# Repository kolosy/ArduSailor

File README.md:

ArduSailor
==========
ArduSailor is an autonomous sail boat project based on the Arduino platform. Using a modified Arduino Mega board (schematics under `layout`), ArduSailor can be programmed with a set of GPS waypoints that it can then sail to.

The platform is built around a simple, two-servo sail boat design, with a winch servo for sail plan control and a rudder servo for steering. The circuit layout included is for a modified Arduino Mega 2560, which includes:

* A 9DOF IMU (an Invensense MPU9250)
* A break-out for a weather vane (this circuit is also included)
* A microSD card
* Two servo breakouts
* Three power regulators (one to provide 6V for the servos, one to provide 3.3V for the rest and one MPPT solar charger for the LiPo)
* A GPS chip (Venus 638FPLx)
* A breakout for a UART-based camera module (currently unused)
* A battery input (currently running from a 3S LiPo battery pack)
* A breakout for the main UART port for logging (on my build I have this routed to a 433MHz radio module)
* ICSP header for programming

The included firmware operates off of a list of GPS waypoints. The pilot steers straight for the next waypoint when it can. When the waypoint is upwind (within `IRONS` of the wind), it beats: close-hauled, zigzagging up a corridor `CORRIDOR` metres either side of the line from where the leg started to the waypoint, tacking at the corridor's edges, until it can lay the waypoint on one tack. To tack, it comes up to just outside the no-go zone (`TACK_MARGIN`) and goes through the wind from there, with way on (`MIN_TACK_SPEED`). If it can't get up to speed there, or its last two tacks ended in irons (`MAX_TACK_TRIES`), it goes round by gybing instead. Whenever the waypoint can be reached on the tack it's on, it steers straight for it. If the boat stops (in irons, or drifting backwards), it lets the sheet out and falls off (`RECOVER_ANGLE`) on whichever tack it's on, steering the other way while it's going backwards. It then stays on that tack, sailing a little free until it's back up to speed, rather than tacking straight back into irons. Outside a beat there is no cross-track correction.

Simulator
=========
`sim/` builds the firmware for your computer and sails it around a simulated course, with the boat, wind, waves and sensors shown in a browser. You can change the conditions, the PID gains and the firmware's settings while it runs. On a Mac (after `xcode-select --install`):

    python3 sim/run.py

See [sim/README.md](sim/README.md).

Status
======
I've built several iterations of the circuit board, and it works reliably. When at speed, the navigation works .. somewhat. My current testing is in a sub-optimal body of water (a long, narrow channel), making certain tests difficult.

Here's what I need to tackle

Short-term
----------
* Finish debugging basic piloting and navigation.
* Add cross-track correction
* Add heel compensation
* Add camera module support

Longer-term
-----------
* Improve the navigation algorithm to include no-go zones
* Add wind speed sensor (hw)

Pie-in-the-sky
--------
I'd like to replace the pilot code entirely with AI. This should be reduce-able to an optimization problem... but that's a bit beyond me right now.

Enjoy!

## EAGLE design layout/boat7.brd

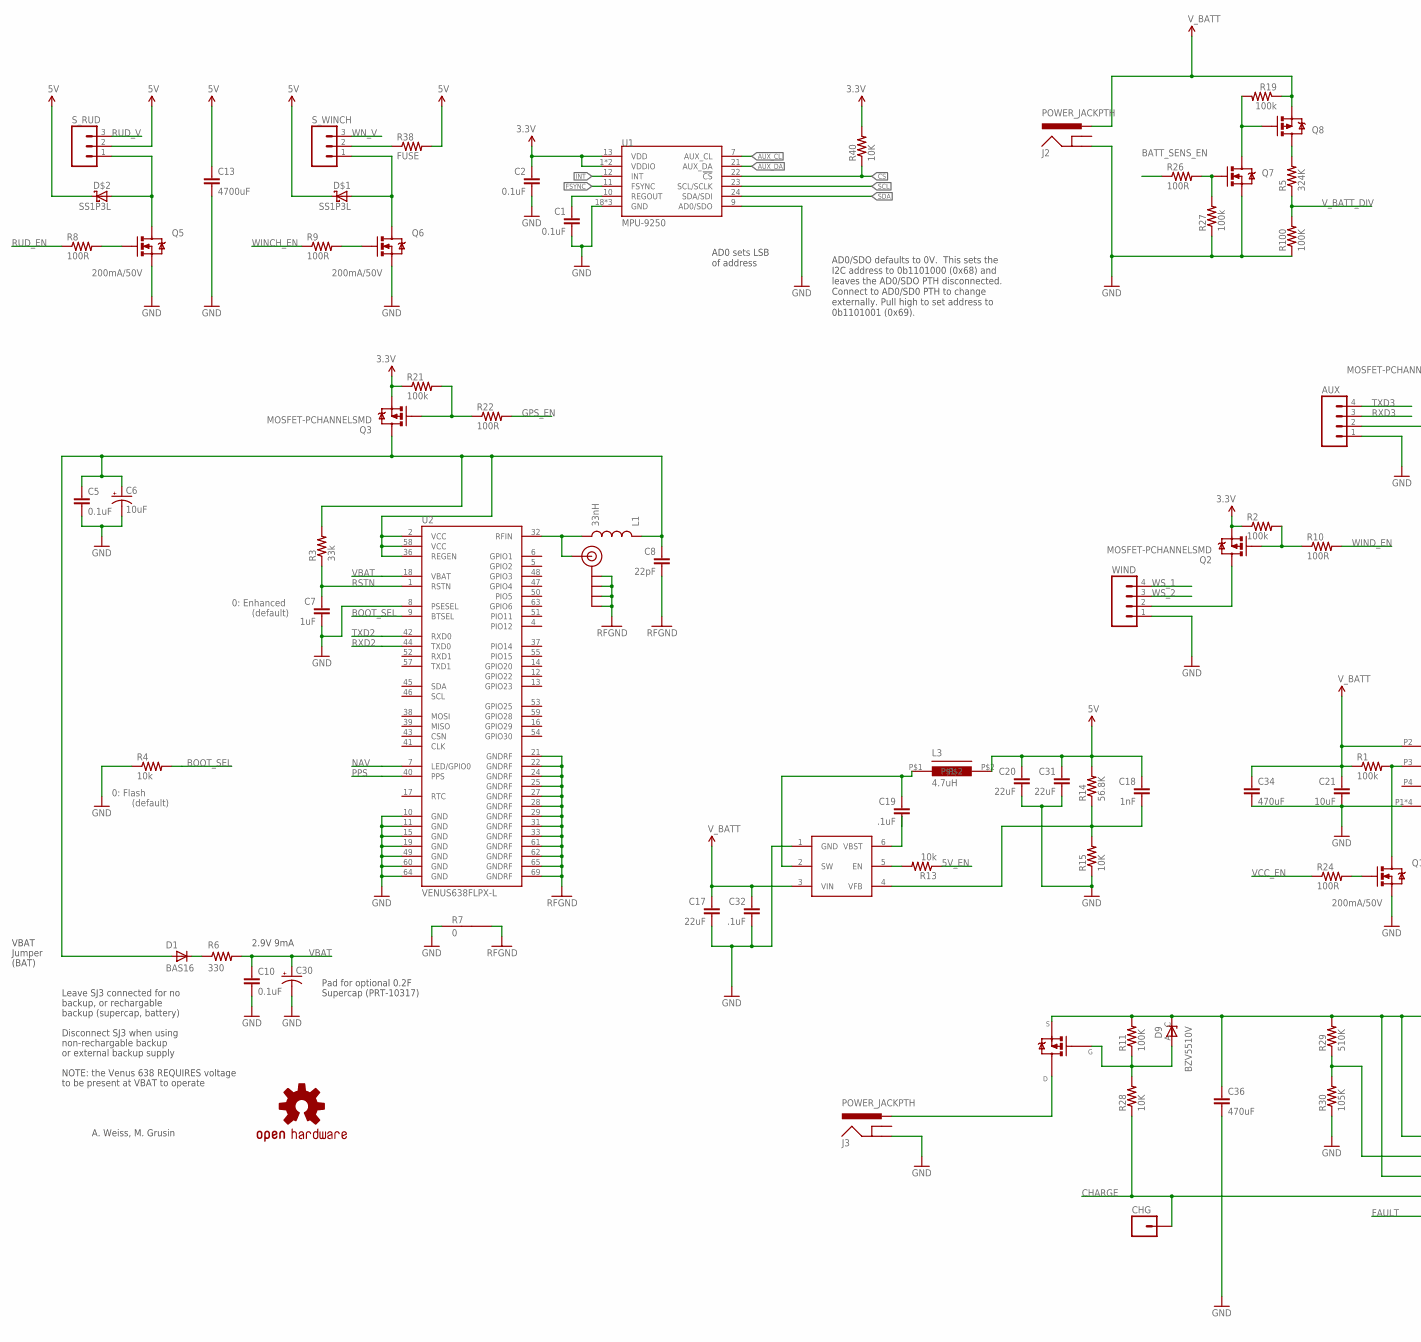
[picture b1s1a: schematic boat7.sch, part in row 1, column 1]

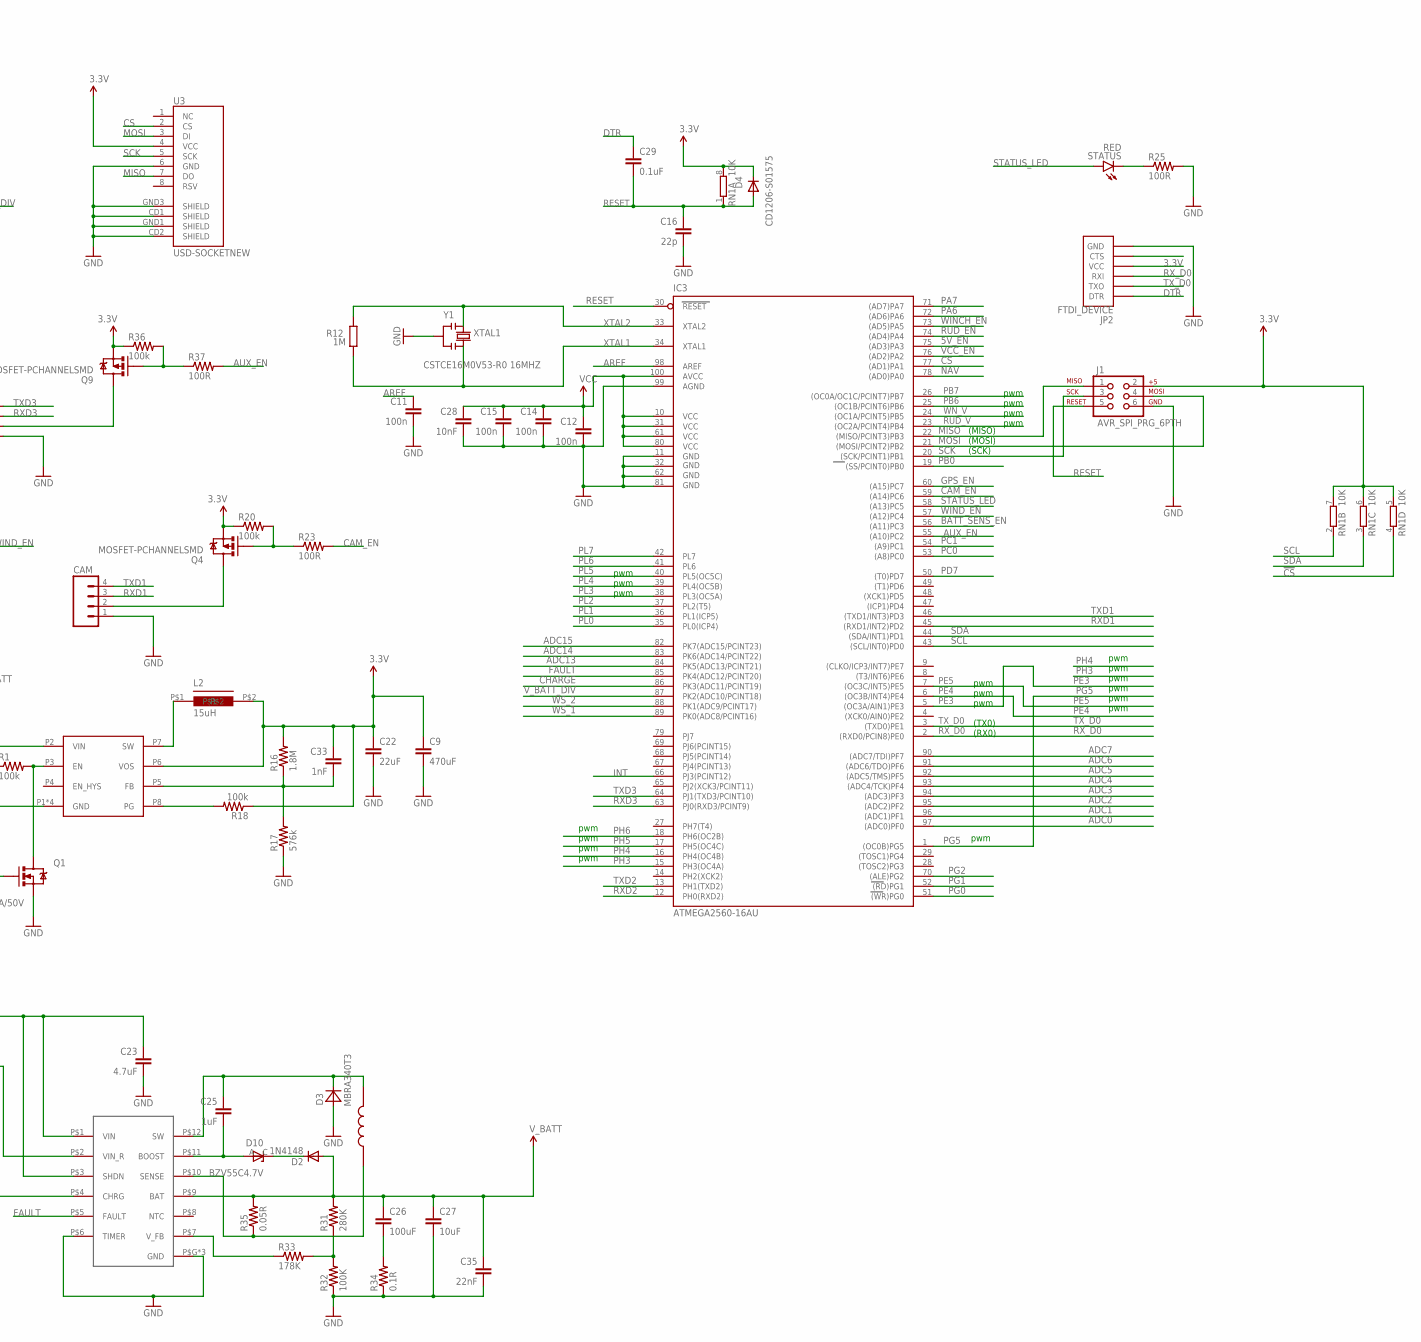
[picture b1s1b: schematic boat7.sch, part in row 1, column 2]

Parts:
AUX: M04PTH; 1X04
C1, C2, C5, C10, C29: 0.1uF; 0603-CAP
C6: 10uF; EIA3216
C7: 1uF; 0603-CAP
C8: 22pF; 0603-CAP
C9, C34, C36: 470uF; CAP-PTH-5MM
C11, C12, C14, C15: 100n; C0603-ROUND
C13: 4700uF; CAP-PTH-5MM
C16: 22p; C0603-ROUND
C17, C20, C31: 22uF; 1206
C18: 1nF; 0805
C19, C32: .1uF; 0805
C21: 10uF; 0805
C22: 22uF; 0805
C23: 4.7uF; 1206
C25: 1uF; 0805
C26: 100uF; 1210
C27: 10uF; 1210
C28: 10nF; 0603-CAP
C30: CAP_POL; DSK-621
C33: 1nF; 0402-CAP
C35: 22nF; 0805
CAM: M04PTH; 1X04
CHG: M01PTH; 1X01
D1: BAS16; SOD-323
D2: 1N4148; MINIMELF
D3: MBRA340T3; SMA
D4: CD1206-S01575; SOD323-R
D9: BZV5510V; MINIMELF
D10: BZV55C4.7V; MINIMELF
D$1, D$2: SS1P3L; MICROSMP
IC3: ATMEGA2560-16AU; TQFP100
J1: AVR_SPI_PRG_6PTH; 2X3
J2, J3: POWER_JACKPTH; POWER_JACK_PTH
JP2: FTDI_DEVICE; FTDI_DEVICE_SIDE
JP5: SMA_EDGE; SMA-EDGE
L1: 33nH; 0603
L2: 15uH; VLCF4020
L3: 4.7uH; SLF7055
Q1, Q5, Q6, Q7: 200mA/50V; SOT23-3
Q2, Q3, Q4, Q8, Q9: MOSFET-PCHANNELSMD; SOT23-3
R1, R2, R18, R19, R20, R21, R27, R36: 100k; 0603-RES
R3: 33k; 0603-RES
R4, R13: 10k; 0603-RES
R5: 324K; 0603-RES
R6: 330; 0603-RES
R7: 0; GND-JUMP
R8, R9, R10, R22, R23, R24, R25, R26, R37: 100R; 0603-RES
R11, R32, R100: 100K; 0603-RES
R12: 1M; R0603-ROUND
R14: 56.8K; 0603-RES
R15, R28, R40: 10K; 0603-RES
R16: 1.8M; 0603-RES
R17: 576k; 0603-RES
R29: 510K; 0603-RES
R30: 105K; 0603-RES
R31: 280K; 0603-RES
R33: 178K; 0603-RES
R34: 0.1R; 1206
R35: 0.05R; 1206
R38: FUSE; AXIAL-0.1
RN1: 10K; CAT16
STATUS: RED; LED-0603
S_RUD: M03PTH; 1X03
S_WINCH: M03PTH; 1X03
U1: MPU-9250; QFN24_PAD
U2: VENUS638FLPX-L; VENUS638FLPX
U3: USD-SOCKETNEW; MICRO-SD-SOCKET-PP
U$1: TPS62125; S-PWSON-N8
U$2: TPS56X200; SOT23-6
U$4: OSHW-LOGOS; OSHW-LOGO-S
U$5: LT365212; 12-LEAD-MSOP-EXPOSED
U$7: B82464G4
U$15: SI4401DDY; SOIC-8
WIND: M04PTH; 1X04
Y1: CSTCE16M0V53-R0 16MHZ; RESONATOR

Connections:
3.3V: C2.1, C9.1, C12.1, C14.1, C15.1, C22.1, C28.1, C33.1, D4.C, IC3.10 (VCC), IC3.31 (VCC1), IC3.61 (VCC2), IC3.80 (VCC3), IC3.100 (AVCC), J1.2, JP2.P$4 (VCC), L2.P$2, Q2.2 (S), Q3.2 (S), Q4.2 (S), Q9.2 (S), R2.1, R16.2, R18.1, R20.1, R21.1, R36.1, R40.2, RN1.5 (2), RN1.6 (2), RN1.7 (2), RN1.8 (2), U1.1 (VDDIO), U1.8 (VDDIO), U1.13 (VDD), U3.4 (VCC), U$1.P6 (VOS)
5V: C13.1, C18.1, C20.1, C31.1, D$1.C, D$2.C, L3.P$2, R14.2, R38.P$2 (2), S_RUD.2
5V_EN: IC3.75 ((AD3)PA3), R13.1
!CS: R40.1, RN1.4 (1), U1.22 (!CS)
ADC0: IC3.97 ((ADC0)PF0)
ADC1: IC3.96 ((ADC1)PF1)
ADC2: IC3.95 ((ADC2)PF2)
ADC3: IC3.94 ((ADC3)PF3)
ADC4: IC3.93 ((ADC4/TCK)PF4)
ADC5: IC3.92 ((ADC5/TMS)PF5)
ADC6: IC3.91 ((ADC6/TDO)PF6)
ADC7: IC3.90 ((ADC7/TDI)PF7)
ADC13: IC3.84 (PK5(ADC13/PCINT21))
ADC14: IC3.83 (PK6(ADC14/PCINT22))
ADC15: IC3.82 (PK7(ADC15/PCINT23))
ANT: JP5.SIG (SIGNAL), L1.2, U2.32 (RFIN)
AREF: C11.1, IC3.98 (AREF)
AUX_CL: U1.7 (AUX_CL)
AUX_DA: U1.21 (AUX_DA)
AUX_EN: IC3.55 ((A10)PC2), R37.2
BAT: C17.1, C21.1, C26.1, C27.1, C32.1, C34.1, C35.1, D2.A, J2.PWR, Q8.2 (S), R1.1, R19.1, R31.2, R35.2, U$1.P2 (VIN), U$2.3 (VIN), U$5.P$9 (BAT)
BATT_SENS_EN: IC3.56 ((A11)PC3), R26.1
BOOST: C25.2, D10.A, U$5.P$11 (BOOST)
BOOT_SEL: R4.2, U2.9 (BTSEL)
CAM_EN: IC3.59 ((A14)PC6), R23.2
CHARGE: CHG.1, IC3.86 (PK3(ADC11/PCINT19)), R28.1, U$5.P$4 (CHRG)
CS: IC3.77 ((AD1)PA1), U3.2 (CS)
DTR: C29.1, JP2.P$1 (DTR)
FAULT: IC3.85 (PK4(ADC12/PCINT20)), U$5.P$5 (FAULT)
FSYNC: U1.11 (FSYNC)
GND: AUX.1, C1.2, C2.2, C5.2, C6.C (-), C7.2, C9.2, C10.2, C11.2, C12.2, C13.2, C14.2, C15.2, C16.2, C17.2, C20.2, C21.2, C22.2, C23.2, C27.2, C28.2, C30.GND (-), C31.2, C32.2, C34.2, C35.2, C36.2, CAM.1, D3.A, IC3.11 (GND), IC3.32 (GND1), IC3.62 (GND2), IC3.81 (GND3), IC3.99 (AGND), J1.6, J2.GND, J3.GND, JP2.P$6 (GND), Q1.2 (S), Q5.2 (S), Q6.2 (S), Q7.2 (S), R4.1, R7.1, R15.1, R17.1, R25.2, R27.1, R30.1, R32.1, R34.1, R100.1, U1.9 (AD0/SDO), U1.18 (GND), U1.20 (GND), U1.CENTER (GND), U2.8 (PSESEL), U2.10 (GND), U2.11 (GND), U2.15 (GND), U2.19 (GND), U2.49 (GND), U2.60 (GND), U2.64 (GND), U3.6 (GND), U3.CD1 (SHIELD), U3.CD2 (SHIELD), U3.GND1 (SHIELD), U3.GND3 (SHIELD), U$1.P1 (GND), U$1.P_THERM (GND), U$1.P_THERM_VIA (GND), U$1.P_THERM_VIA1 (GND), U$2.1 (GND), U$5.P$6 (TIMER), U$5.P$G (GND), U$5.P$G1 (GND), U$5.P$G2 (GND), WIND.1, Y1.2
GPS_EN: IC3.60 ((A15)PC7), R22.2
GPS_PWR: C5.1, C6.A (+), C8.1, D1.2 (A), L1.1, Q3.3 (D), R3.2, U2.2 (VCC), U2.36 (REGEN), U2.58 (VCC)
INT: IC3.66 (PJ3(PCINT12)), U1.12 (INT)
MISO: IC3.22 ((MISO/PCINT3)PB3), J1.1, U3.7 (DO)
MOSI: IC3.21 ((MOSI/PCINT2)PB2), J1.4, U3.3 (DI)
unnamed: R38.P$1 (1), S_WINCH.2
unnamed: AUX.2, Q9.3 (D)
unnamed: C23.1, C36.1, D9.C (K), R11.2, R29.2, U$5.P$1 (VIN), U$5.P$3 (SHDN), U$15.1 (S), U$15.2 (S), U$15.3 (S)
unnamed: D1.1 (C), R6.1
unnamed: D9.A, R11.1, R28.2, U$15.4 (G)
unnamed: Q5.1 (G), R8.2
unnamed: D$1.A, Q6.3 (D), S_WINCH.1
unnamed: D$2.A, Q5.3 (D), S_RUD.1
unnamed: Q6.1 (G), R9.2
unnamed: C19.1, L3.P$1, U$2.2 (SW)
unnamed: Q9.1 (G), R36.2, R37.1
unnamed: R31.1, R32.2, R33.2
unnamed: L2.P$1, U$1.P7 (SW)
unnamed: R13.2, U$2.5 (EN)
unnamed: C33.2, R16.1, R17.2, U$1.P5 (FB)
unnamed: R18.2, U$1.P8 (PG)
unnamed: C18.2, R14.1, R15.2, U$2.4 (VFB)
unnamed: CAM.2, Q4.3 (D)
unnamed: Q4.1 (G), R20.2, R23.1
unnamed: Q3.1 (G), R21.2, R22.1
unnamed: Q1.3 (D), R1.2, U$1.P3 (EN)
unnamed: Q1.1 (G), R24.2
unnamed: Q2.3 (D), WIND.2
unnamed: R25.1, STATUS.C
unnamed: Q2.1 (G), R2.2, R10.1
unnamed: Q8.3 (D), R5.2
unnamed: Q7.3 (D), Q8.1 (G), R19.2
unnamed: Q7.1 (G), R26.2, R27.2
unnamed: C19.2, U$2.6 (VBST)
unnamed: C26.2, R34.2
unnamed: D2.C, D10.C (K)
NAV: IC3.78 ((AD0)PA0), U2.7 (LED/GPIO0)
PA6: IC3.72 ((AD6)PA6)
PA7: IC3.71 ((AD7)PA7)
PB0: IC3.19 ((SS/PCINT0)PB0)
PB6: IC3.25 ((OC1B/PCINT6)PB6)
PB7: IC3.26 ((OC0A/OC1C/PCINT7)PB7)
PC0: IC3.53 ((A8)PC0)
PC1: IC3.54 ((A9)PC1)
PD7: IC3.50 ((T0)PD7)
PE3: IC3.5 ((OC3A/AIN1)PE3)
PE4: IC3.6 ((OC3B/INT4)PE4)
PE5: IC3.7 ((OC3C/INT5)PE5)
PG0: IC3.51 ((WR)PG0)
PG1: IC3.52 ((RD)PG1)
PG2: IC3.70 ((ALE)PG2)
PG5: IC3.1 ((OC0B)PG5)
PH3: IC3.15 (PH3(OC4A))
PH4: IC3.16 (PH4(OC4B))
PH5: IC3.17 (PH5(OC4C))
PH6: IC3.18 (PH6(OC2B))
PL0: IC3.35 (PL0(ICP4))
PL1: IC3.36 (PL1(ICP5))
PL2: IC3.37 (PL2(T5))
PL3: IC3.38 (PL3(OC5A))
PL4: IC3.39 (PL4(OC5B))
PL5: IC3.40 (PL5(OC5C))
PL6: IC3.41 (PL6)
PL7: IC3.42 (PL7)
PPS: U2.40 (PPS)
REGOUT: C1.1, U1.10 (REGOUT)
RESET: C16.1, C29.2, D4.A, IC3.30 (RESET), J1.5, RN1.1
RFGND: C8.2, JP5.GND@0 (GND), JP5.GND@1 (GND), JP5.GND@2 (GND), JP5.GND@3 (GND), R7.2, U2.21 (GNDRF), U2.22 (GNDRF), U2.24 (GNDRF), U2.25 (GNDRF), U2.27 (GNDRF), U2.28 (GNDRF), U2.29 (GNDRF), U2.31 (GNDRF), U2.33 (GNDRF), U2.61 (GNDRF), U2.62 (GNDRF), U2.65 (GNDRF), U2.69 (GNDRF)
RSTN: C7.1, R3.1, U2.1 (RSTN)
RUD_EN: IC3.74 ((AD4)PA4), R8.1
RUD_V: IC3.23 ((OC2A/PCINT4)PB4), S_RUD.3
RXD1: CAM.3, IC3.45 ((RXD1/INT2)PD2)
RXD2: IC3.12 (PH0(RXD2)), U2.44 (TXD0)
RXD3: AUX.3, IC3.63 (PJ0(RXD3/PCINT9))
RX_D0: IC3.2 ((RXD0/PCIN8)PE0), JP2.P$3 (RXI)
SCK: IC3.20 ((SCK/PCINT1)PB1), J1.3, U3.5 (SCK)
SCL: IC3.43 ((SCL/INT0)PD0), RN1.2 (1), U1.23 (SCL/SCLK)
SDA: IC3.44 ((SDA/INT1)PD1), RN1.3 (1), U1.24 (SDA/SDI)
SENSE: R35.1, U$5.P$10 (SENSE), U$7.P$1
STATUS_LED: IC3.58 ((A13)PC5), STATUS.A
SW: C25.1, D3.C, U$5.P$12 (SW), U$7.P$2
S_IN: J3.PWR, U$15.5 (D), U$15.6 (D), U$15.7 (D), U$15.8 (D)
TXD1: CAM.4, IC3.46 ((TXD1/INT3)PD3)
TXD2: IC3.13 (PH1(TXD2)), U2.42 (RXD0)
TXD3: AUX.4, IC3.64 (PJ1(TXD3/PCINT10))
TX_D0: IC3.3 ((TXD0)PE1), JP2.P$2 (TXO)
VBAT: C10.1, C30.VCC (+), R6.2, U2.18 (VBAT)
VCC_EN: IC3.76 ((AD2)PA2), R24.1
VFB: R33.1, U$5.P$7 (V_FB)
VINR: R29.1, R30.2, U$5.P$2 (VIN_R)
V_BATT_DIV: IC3.87 (PK2(ADC10/PCINT18)), R5.1, R100.2
WINCH_EN: IC3.73 ((AD5)PA5), R9.1
WIND_EN: IC3.57 ((A12)PC4), R10.2
WN_V: IC3.24 ((OC1A/PCINT5)PB5), S_WINCH.3
WS_1: IC3.89 (PK0(ADC8/PCINT16)), WIND.4
WS_2: IC3.88 (PK1(ADC9/PCINT17)), WIND.3
XTAL1: IC3.34 (XTAL1), R12.1, Y1.3
XTAL2: IC3.33 (XTAL2), R12.2, Y1.1

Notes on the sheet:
RFGND
0: Enhanced
0: Flash
(default)
A. Weiss, M. Grusin
Supercap (PRT-10317)
Pad for optional 0.2F
2.9V 9mA
VBAT
Jumper
(BAT)
Leave SJ3 connected for no
backup, or rechargable
backup (supercap, battery)
Disconnect SJ3 when using
non-rechargable backup
or external backup supply
NOTE: the Venus 638 REQUIRES voltage
to be present at VBAT to operate
pwm
(TX0)
(RX0)
(MISO)
(SCK)
(MOSI)
AD0/SDO defaults to 0V. This sets the I2C address to 0b1101000 (0x68) and leaves the AD0/SDO PTH disconnected. Connect to AD0/SD0 PTH to change externally. Pull high to set address to 0b1101001 (0x69).
AD0 sets LSB of address

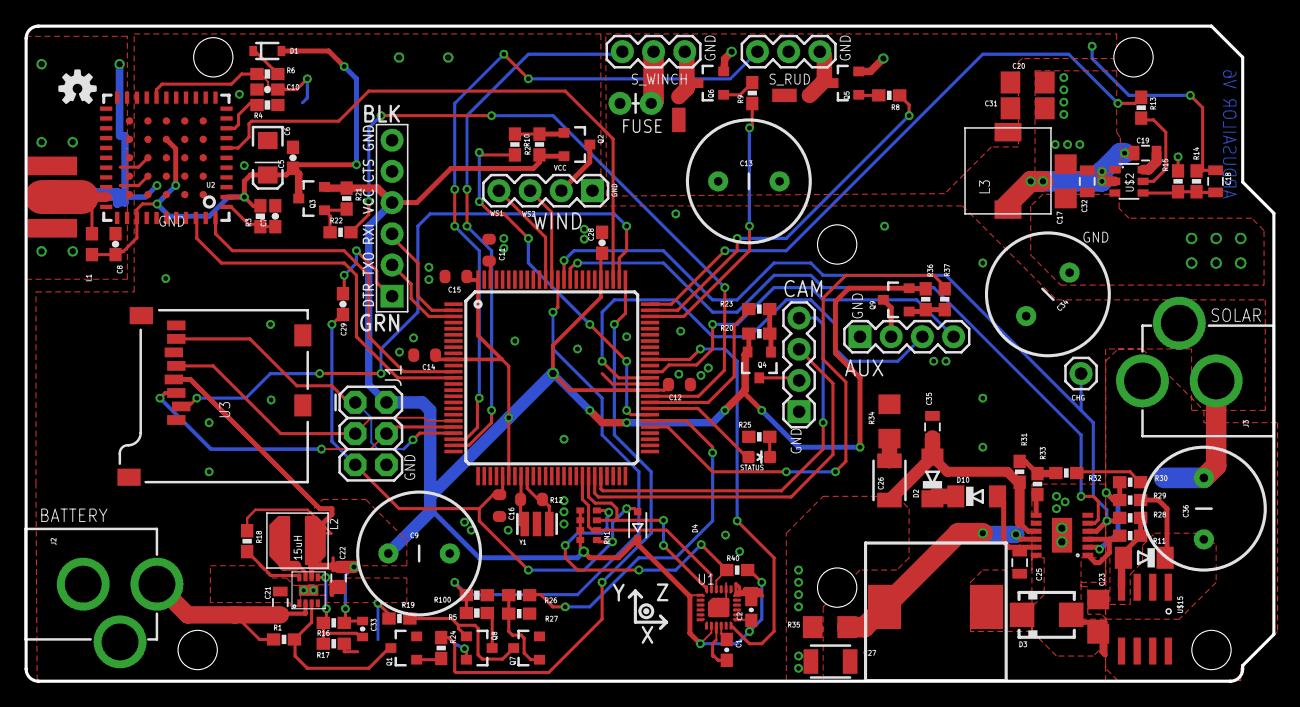
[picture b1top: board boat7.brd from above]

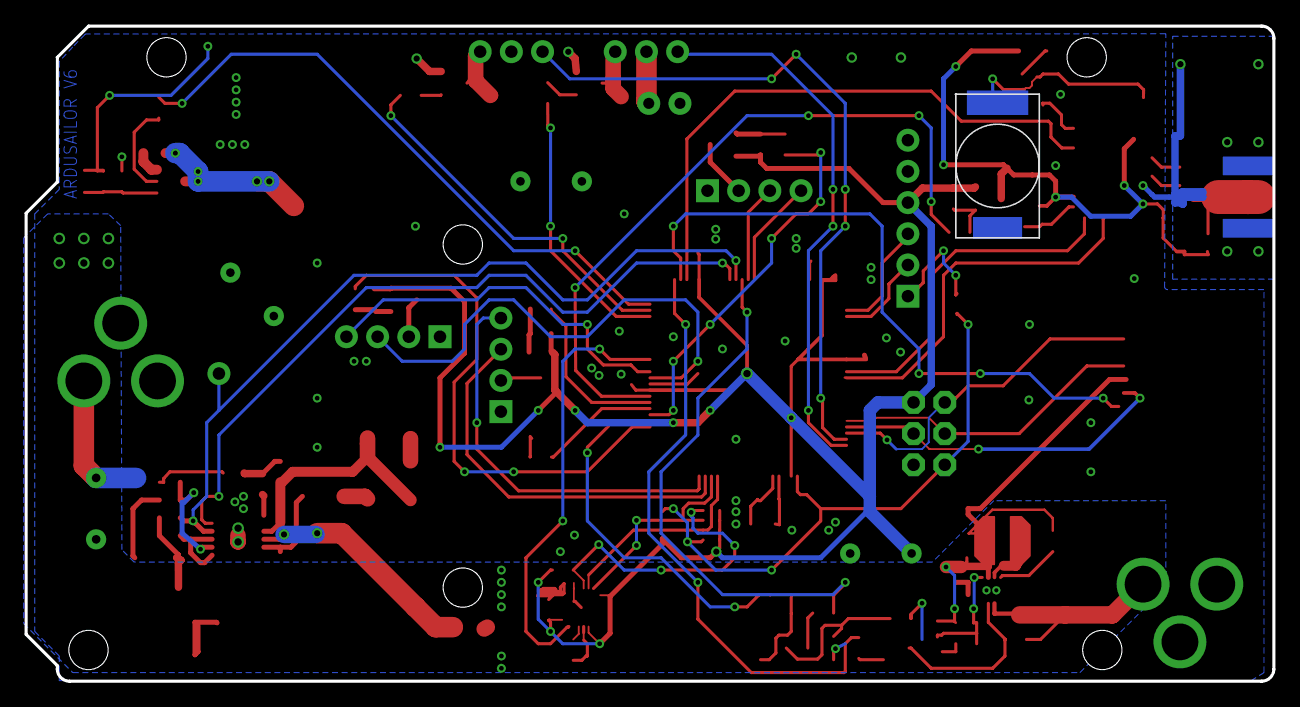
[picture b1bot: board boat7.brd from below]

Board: 2 copper layers, 101.6 x 53.3 mm, 117 parts (2 on the bottom side), 87 nets.

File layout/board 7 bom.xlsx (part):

Kit Qty | Shrinkage | 2 | Value | Device | Package | Parts | DigiKey | Search Link | Description MF MPN OC_FARNELL OC_NEWARK PROD_ID VALUE
1 | 10 | 20 | 330 | RESISTOR0603-RES | 0603-RES | R6 | 311-330GRCT-ND | http://www.digikey.com/product-search/en?keywords=311-330GRCT-ND | Resistor
2 | 10 | 40 | .1uF | CAP0805 | 805 | C19, C32 | 445-8183-1-ND | http://www.digikey.com/product-search/en?keywords=445-8183-1-ND | Capacitor
1 | 10 | 20 | 0.05R | RESISTOR1206 | 1206 | R35 | 311-.05LYCT-ND | http://www.digikey.com/product-search/en?keywords=311-.05LYCT-ND | Resistor
1 | 10 | 20 | 0.1R | RESISTOR1206 | 1206 | R34 | 989-1031-1-ND | http://www.digikey.com/product-search/en?keywords=989-1031-1-ND | Resistor
9 | 1.5 | 27 | 0.1uF | CAP0603-CAP | 0603-CAP | C5, C10, C29, C1, C2, C11, C12, C14, C15 | 445-8136-1-ND | http://www.digikey.com/product-search/en?keywords=445-8136-1-ND | Capacitor
1 | 5 | 10 | 1.8M | RESISTOR0603 | 0603-RES | R16 | 311-1.8MGRCT-ND | http://www.digikey.com/product-search/en?keywords=311-1.8MGRCT-ND | Resistor
11 | 1.5 | 33 | 100K | RESISTOR0603 | 0603-RES | R11, R32, R100, R1, R2, R18, R19, R20, R21, R27, R36 | 311-100KGRCT-ND | http://www.digikey.com/product-search/en?keywords=311-100KGRCT-ND | Resistor
9 | 1.5 | 27 | 100R | RESISTOR0603 | 0603-RES | R8, R9, R10, R22, R23, R24, R25, R26, R37 | 311-100GRCT-ND | http://www.digikey.com/product-search/en?keywords=311-100GRCT-ND | Resistor
1 | 10 | 20 | 100uF | CAP1210 | 1210 | C26 | 587-3152-1-ND | http://www.digikey.com/product-search/en?keywords=587-3152-1-ND | Capacitor
1 | 10 | 20 | 105K | RESISTOR0603 | 0603-RES | R30 | P105KHCT-ND | http://www.digikey.com/product-search/en?keywords=P105KHCT-ND | Resistor
1 | 10 | 20 | 10K | 4R-NCAT16 | CAT16 | RN1 | CAT16-103J4LFCT-ND | http://www.digikey.com/product-search/en?keywords=CAT16-103J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 | Array Chip Resistor unknown unknown
5 | 1.5 | 15 | 10K | RESISTOR0603 | 0603-RES | R15, R28, R13, R4, R40 | P10.0KHCT-ND | http://www.digikey.com/product-search/en?keywords=P10.0KHCT-ND | Resistor
1 | 10 | 20 | 10nF | CAP0603-CAP | 0603-CAP | C28 | 445-1311-1-ND | http://www.digikey.com/product-search/en?keywords=445-1311-1-ND | Capacitor
1 | 10 | 20 | 10uF | CAP_POL1206 | EIA3216 | C6 | 718-1969-1-ND | http://www.digikey.com/product-search/en?keywords=718-1969-1-ND | Capacitor Polarized
1 | 10 | 20 | 10uF | CAP0805 | 805 | C21 | 445-14387-1-ND | http://www.digikey.com/product-search/en?keywords=445-14387-1-ND | Capacitor
1 | 10 | 20 | 10uF | CAP1210 | 1210 | C27 | 445-1434-1-ND | http://www.digikey.com/product-search/en?keywords=445-1434-1-ND | Capacitor
1 | 10 | 20 | 15uH | VLCF4020 | VLCF4020 | L2 | 445-3187-1-ND | http://www.digikey.com/product-search/en?keywords=445-3187-1-ND
1 | 10 | 20 | 178K | RESISTOR0603 | 0603-RES | R33 | P178KDBCT-ND | http://www.digikey.com/product-search/en?keywords=P178KDBCT-ND | Resistor
1 | 10 | 20 | 1M | R-EU_R0603 | R0603-ROUND | R12 | RHM1.00MAYCT-ND | http://www.digikey.com/product-search/en?keywords=RHM1.00MAYCT-ND | RESISTOR, European symbol
1 | 10 | 20 | 1N4148 | 1N4148 | MINIMELF | D2 | DL4148-TPMSCT-ND | http://www.digikey.com/product-search/en?keywords=DL4148-TPMSCT-ND | DIODE
1 | 10 | 20 | 1nF | CAP0402-CAP | 0402-CAP | C33 | 445-8083-1-ND | http://www.digikey.com/product-search/en?keywords=445-8083-1-ND | Capacitor
1 | 10 | 20 | 1nF | CAP0805 | 805 | C18 | 399-7987-1-ND | http://www.digikey.com/product-search/en?keywords=399-7987-1-ND | Capacitor
1 | 10 | 20 | 1uF | CAP0603-CAP | 0603-CAP | C7 | 445-1604-1-ND | http://www.digikey.com/product-search/en?keywords=445-1604-1-ND | Capacitor
1 | 10 | 20 | 1uF | CAP0805 | 805 | C25 | 490-1695-1-ND | http://www.digikey.com/product-search/en?keywords=490-1695-1-ND | Capacitor
4 | 1.5 | 12 | 200mA/50V | MOSFET-NCHANNELBSS138 | SOT23-3 | Q1, Q5, Q6, Q7 | SSM3K329RLFCT-ND | http://www.digikey.com/product-search/en?keywords=SSM3K329RLFCT-ND | Common NMOSFET Parts TRANS-00830 200mA/50V
1 | 10 | 20 | 22nF | CAP0805 | 805 | C35 | 445-1345-1-ND | http://www.digikey.com/product-search/en?keywords=445-1345-1-ND | Capacitor
2 | 10 | 40 | 22pF | C-EU0603-RND | C0603-ROUND | C16, C8 | 445-1273-1-ND | http://www.digikey.com/product-search/en?keywords=445-1273-1-ND | CAPACITOR, European symbol
1 | 10 | 20 | 22uF | CAP0805 | 805 | C22 | 445-14374-1-ND | http://www.digikey.com/product-search/en?keywords=445-14374-1-ND | Capacitor
3 | 5 | 30 | 22uF | CAP1206 | 1206 | C17, C20, C31 | 1276-3047-1-ND | http://www.digikey.com/product-search/en?keywords=1276-3047-1-ND | Capacitor
1 | 10 | 20 | 280K | RESISTOR0603 | 0603-RES | R31 | 311-280KHRCT-ND | http://www.digikey.com/product-search/en?keywords=311-280KHRCT-ND | Resistor
1 | 10 | 20 | 324K | RESISTOR0603-RES | 0603-RES | R5 | 311-324KHRCT-ND | http://www.digikey.com/product-search/en?keywords=311-324KHRCT-ND | Resistor
1 | 10 | 20 | 33k | RESISTOR0603-RES | 0603-RES | R3 | 311-33KGRCT-ND | http://www.digikey.com/product-search/en?keywords=311-33KGRCT-ND | Resistor
1 | 10 | 20 | 33nH | INDUCTOR0603 | 603 | L1 | 712-1440-1-ND | http://www.digikey.com/product-search/en?keywords=712-1440-1-ND | Inductors
1 | 10 | 20 | 4.7uF | CAP1206 | 1206 | C23 | 490-6521-1-ND | http://www.digikey.com/product-search/en?keywords=490-6521-1-ND | Capacitor
1 | 10 | 20 | 4.7uH | SLF60287055 | SLF7055 | L3 | 445-4563-1-ND | http://www.digikey.com/product-search/en?keywords=445-4563-1-ND
1 | 1 | 2 | 4700uF | CAPPTH1 | CAP-PTH-5MM | C13 | P5130-ND | http://www.digikey.com/product-search/en?keywords=P5130-ND | Capacitor
3 | 1 | 6 | 470uF | CAPPTH1 | CAP-PTH-5MM | C34, C36, C9 | 338-1703-ND | http://www.digikey.com/product-search/en?keywords=338-1703-ND | Capacitor
1 | 10 | 20 | 510K | RESISTOR0603 | 0603-RES | R29 | P510KHCT-ND | http://www.digikey.com/product-search/en?keywords=P510KHCT-ND | Resistor
1 | 10 | 20 | 56.8K | RESISTOR0603 | 0603-RES | R14 | 311-56.2KHRCT-ND | http://www.digikey.com/product-search/en?keywords=311-56.2KHRCT-ND | Resistor
1 | 10 | 20 | 576k | RESISTOR0603 | 0603-RES | R17 | 311-576KHRCT-ND | http://www.digikey.com/product-search/en?keywords=311-576KHRCT-ND | Resistor
1 | 1 | 2 | ATMEGA2560-16AU | ATMEGA25602560-16AU | TQFP100 | IC3 | ATMEGA2560V-8AU-ND | http://www.digikey.com/product-search/en?keywords=ATMEGA2560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 | MICROCONTROLLER
1 | 1 | 2 | B82464G4 | B82464G4 | B82464G4 | U$7 | 495-1796-1-ND | http://www.digikey.com/product-search/en?keywords=495-1796-1-ND
2 | 1.5 | 6 | BAS16 | DIODESOD | SOD-323 | D1, D4 | BAS16HT1GCT-ND | http://www.digikey.com/product-search/en?keywords=BAS16HT1GCT-ND | Diode
1 | 1.5 | 3 | BZV5510V | BZV55 | MINIMELF | D9 | BZV55C10-TPMSCT-ND | http://www.digikey.com/product-search/en?keywords=BZV55C10-T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
1 | 1.5 | 3 | BZV55C4.7V | BZV55 | MINIMELF | D10 | BZV55C4V7-TPMSCT-ND | http://www.digikey.com/product-search/en?keywords=BZV55C4V7-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
1 | 1.5 | 3 | CSTCE16M0V53-R0 16MHZ | RESONATORMU | RESONATOR | Y1 | 490-5994-1-ND | http://www.digikey.com/product-search/en?keywords=490-5994-1-ND
1 | 1.5 | 3 | FUSE | RESISTORPTH-1/4W-VERT | AXIAL-0.1 | R38 | F2438-ND | http://www.digikey.com/product-search/en?keywords=F2438-ND | Resistor
1 | 1 | 2 | LT365212 | LT365212 | 12-LEAD-MSOP-EXPOSED | U$5 | LT3652HVEMSE#PBF-ND | http://www.digikey.com/product-search/en?keywords=LT3652HVEM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 | The LT®3652 is a complete monolithic step-down battery
1 | 1.5 | 3 | MBRS340 | MBRS340 | DO214BA | D8 | MBRS340T3GOSCT-ND | http://www.digikey.com/product-search/en?keywords=MBRS340T3G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
5 | 1.5 | 15 | MOSFET-PCHANNELSMD | MOSFET-PCHANNELSMD | SOT23-3 | Q2, Q3, Q4, Q8, Q9 | SSM3J328RLFCT-ND | http://www.digikey.com/product-search/en?keywords=SSM3J328RLFCT-ND | Generic PMOSFET
1 | 1 | 2 | MPU-9250 | MPU-9250 | QFN24_PAD | U1 | 1428-1019-1-ND | http://www.digikey.com/product-search/en?keywords=1428-1019-1-ND | NC pin 19. 2-6 & 14-17 not internally connected. May be used for PCB trace rout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

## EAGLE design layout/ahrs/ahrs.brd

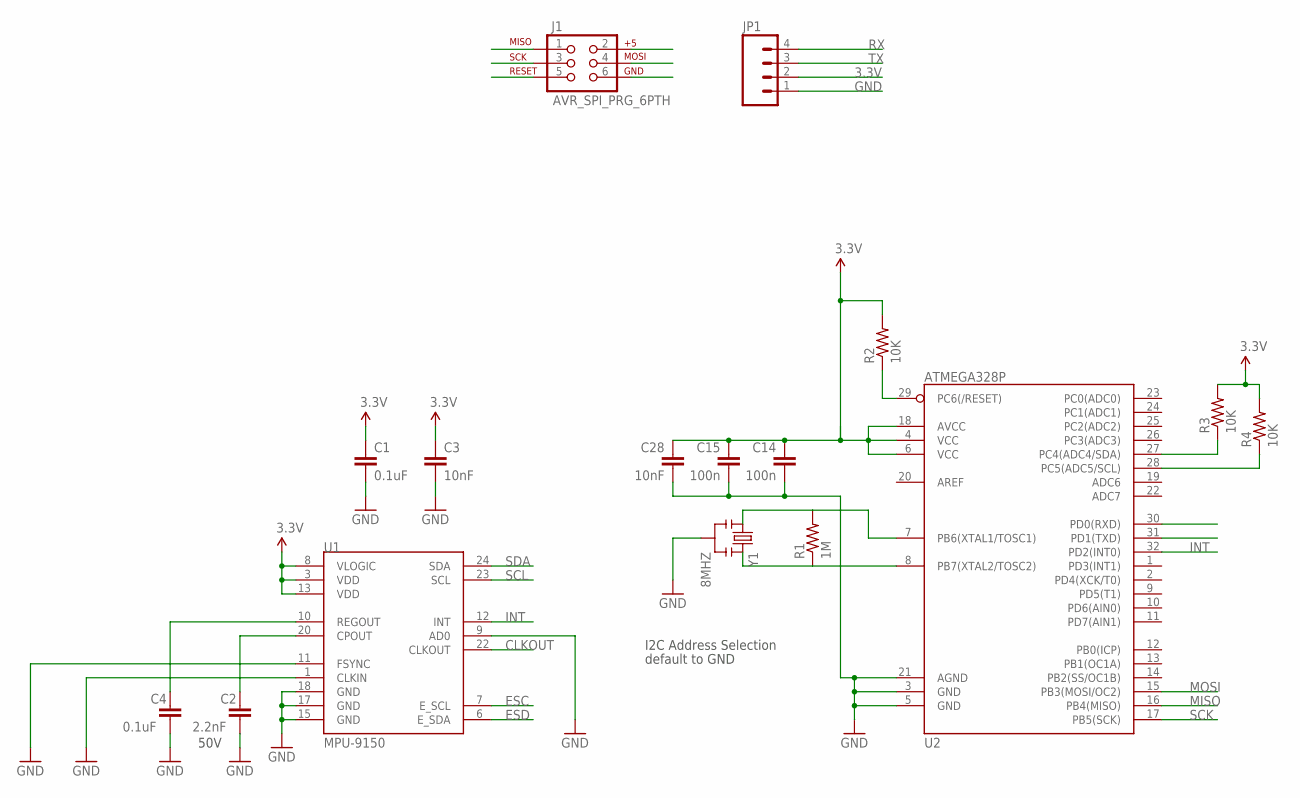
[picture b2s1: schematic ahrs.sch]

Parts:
C1, C4: 0.1uF; 0603-CAP
C2: 2.2nF; 0603-CAP
C3, C28: 10nF; 0603-CAP
C14, C15: 100n; C0603-ROUND
J1: AVR_SPI_PRG_6PTH; 2X3
JP1: M04PTH; 1X04
R1: 1M; 0603-RES
R2, R3, R4: 10K; 0603-RES
U1: MPU-9150; QFN-24-NP
U2: ATMEGA328P; TQFP32-08
Y1: 8MHZ; RESONATOR-SMD

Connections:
3.3V: C1.1, C3.1, C14.1, C15.1, C28.1, J1.2, JP1.2, R2.2, R3.2, R4.2, U1.3 (VDD), U1.8 (VLOGIC), U1.13 (VDD), U2.4 (VCC), U2.6 (VCC), U2.18 (AVCC)
CLKOUT: U1.22 (CLKOUT)
ESC: U1.7 (E_SCL)
ESD: U1.6 (E_SDA)
GND: C1.2, C2.2, C3.2, C4.2, C14.2, C15.2, C28.2, J1.6, JP1.1, U1.1 (CLKIN), U1.9 (AD0), U1.11 (FSYNC), U1.15 (GND), U1.17 (GND), U1.18 (GND), U2.3 (GND), U2.5 (GND), U2.21 (AGND), Y1.2
INT: U1.12 (INT), U2.32 (PD2(INT0))
MISO: J1.1, U2.16 (PB4(MISO))
MOSI: J1.4, U2.15 (PB3(MOSI/OC2))
unnamed: C2.1, U1.20 (CPOUT)
unnamed: C4.1, U1.10 (REGOUT)
unnamed: R1.2, U2.7 (PB6(XTAL1/TOSC1)), Y1.1
unnamed: R1.1, U2.8 (PB7(XTAL2/TOSC2)), Y1.3
RESET: J1.5, R2.1, U2.29 (PC6(/RESET))
RX: JP1.4, U2.30 (PD0(RXD))
SCK: J1.3, U2.17 (PB5(SCK))
SCL: R4.1, U1.23 (SCL), U2.28 (PC5(ADC5/SCL))
SDA: R3.1, U1.24 (SDA), U2.27 (PC4(ADC4/SDA))
TX: JP1.3, U2.31 (PD1(TXD))

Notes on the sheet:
50V
I2C Address Selection
default to GND

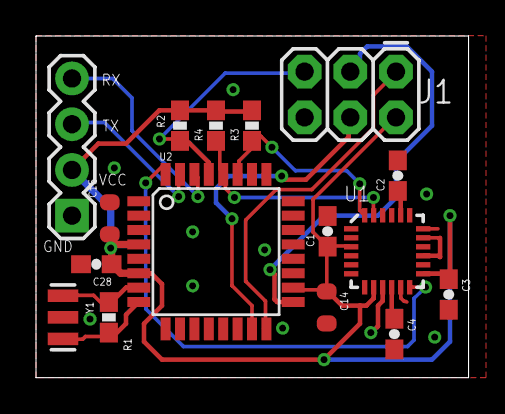
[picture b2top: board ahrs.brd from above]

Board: 2 copper layers, 24.0 x 19.0 mm, 16 parts (0 on the bottom side), 15 nets.

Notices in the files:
parts and their libraries:
SparkFun-Sensors: Licensing: CC v3.0 Share-Alike You are welcome to use this library for commercial purposes.
